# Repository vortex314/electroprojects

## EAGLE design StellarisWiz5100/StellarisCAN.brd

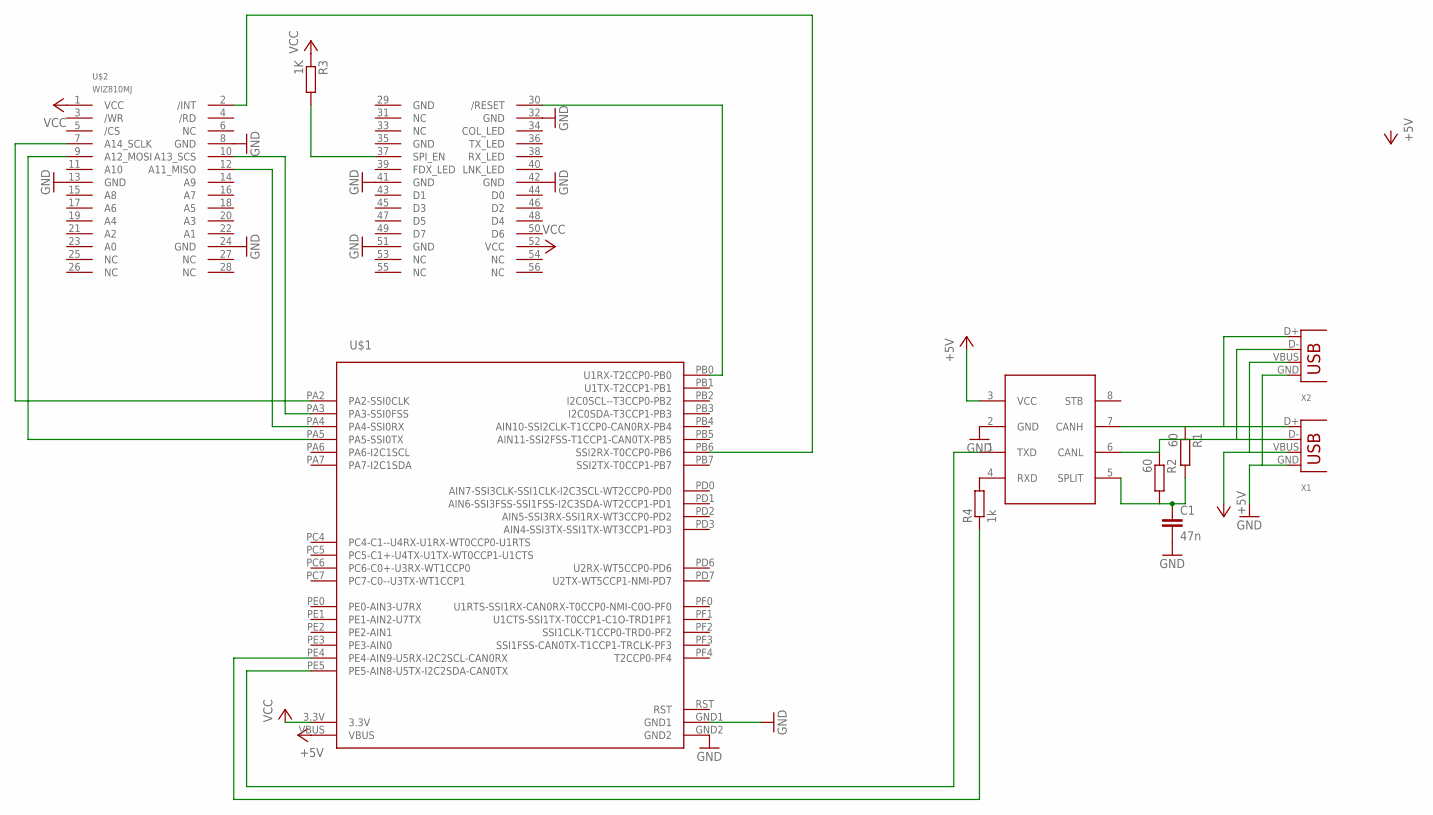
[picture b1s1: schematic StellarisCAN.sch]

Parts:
C1: 47n; C025-040X050
R1, R2: 60; 0207/7
R3: 1K; 0207/7
R4: 1k; 0207/7
U$1: STELLARIS-LAUNCHPADSTELLARIS-LAUNCHPAD-XL; LAUNCHPAD-XL
U$2: WIZ810MJ
U$3: TJA1040; SOIC8-N_MC
X1: USB-A-H
X2: USB-B-H

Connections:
3.3V: U$1.3.3V
+5V: U$1.VBUS, U$3.3 (VCC), X1.VBUS, X2.VBUS
GND: C1.2, U$1.GND1, U$1.GND2, U$2.8 (GND), U$2.13 (GND), U$2.24 (GND), U$2.32 (GND), U$2.41 (GND), U$2.42 (GND), U$2.51 (GND), U$3.2 (GND), X1.GND, X2.GND
unnamed: U$1.PB0 (U1RX-T2CCP0-PB0), U$2.30 (/RESET)
unnamed: R4.2, U$3.4 (RXD)
unnamed: U$1.PA2 (PA2-SSI0CLK), U$2.7 (A14_SCLK)
unnamed: R4.1, U$1.PE4 (PE4-AIN9-U5RX-I2C2SCL-CAN0RX)
unnamed: R1.1, U$3.7 (CANH), X1.D+, X2.D+
unnamed: U$1.PA5 (PA5-SSI0TX), U$2.9 (A12_MOSI)
unnamed: U$1.PE5 (PE5-AIN8-U5TX-I2C2SDA-CAN0TX), U$3.1 (TXD)
unnamed: U$1.PA4 (PA4-SSI0RX), U$2.12 (A11_MISO)
unnamed: U$1.PA3 (PA3-SSI0FSS), U$2.10 (A13_SCS)
unnamed: R3.2, U$2.37 (SPI_EN)
unnamed: C1.1, R1.2, R2.2, U$3.5 (SPLIT)
unnamed: R2.1, U$3.6 (CANL), X1.D-, X2.D-
unnamed: U$1.PB6 (SSI2RX-T0CCP0-PB6), U$2.2 (/INT)
RST: U$1.RST
VCC: R3.1, U$2.1 (VCC), U$2.52 (VCC)

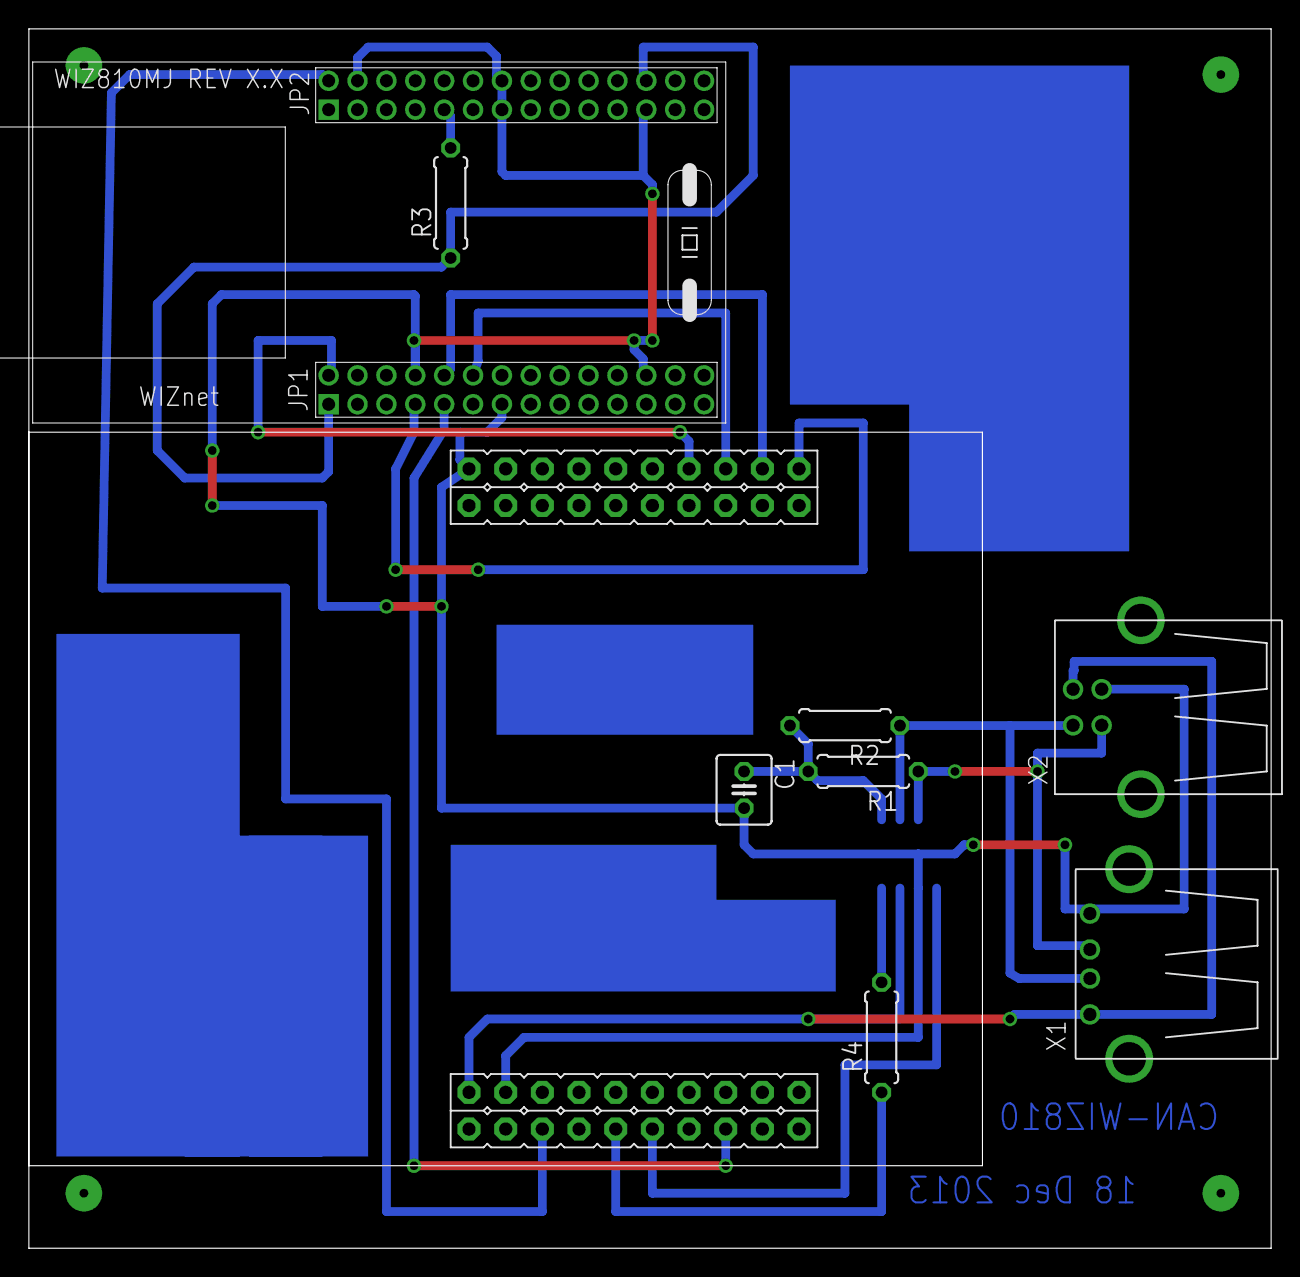
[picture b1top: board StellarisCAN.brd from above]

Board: 2 copper layers, 86.0 x 84.4 mm, 10 parts (1 on the bottom side), 16 nets.

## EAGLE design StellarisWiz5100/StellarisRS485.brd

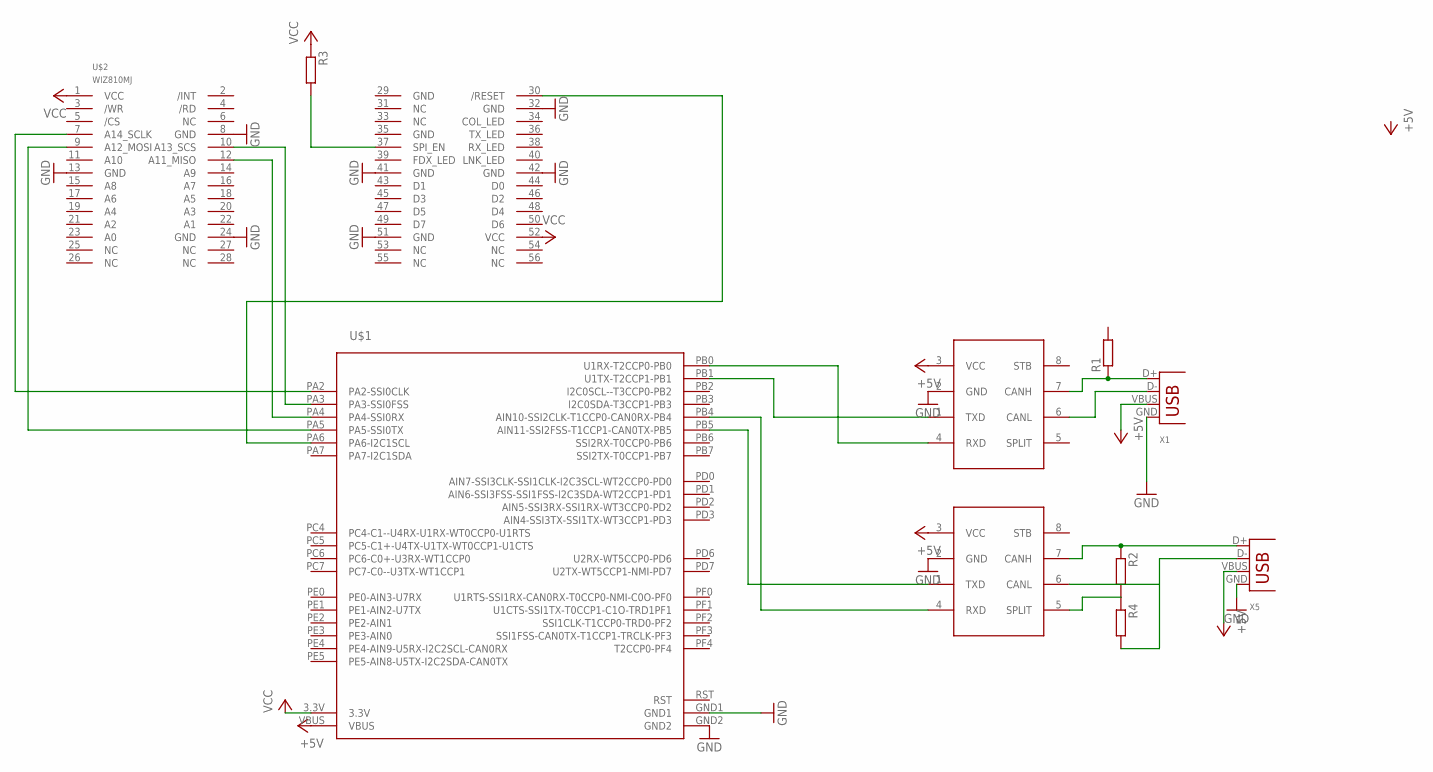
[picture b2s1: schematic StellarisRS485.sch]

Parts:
R1, R2, R3, R4: R-EU_0207/7; 0207/7
U$1: STELLARIS-LAUNCHPADSTELLARIS-LAUNCHPAD-XL; LAUNCHPAD-XL
U$2: WIZ810MJ
U$3, U$4: TJA1040; SOIC8-N_MC
X1, X5: USB-A-H

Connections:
3.3V: U$1.3.3V
+5V: U$1.VBUS, U$3.3 (VCC), U$4.3 (VCC), X1.VBUS, X5.VBUS
GND: U$1.GND1, U$1.GND2, U$2.8 (GND), U$2.13 (GND), U$2.24 (GND), U$2.32 (GND), U$2.41 (GND), U$2.42 (GND), U$2.51 (GND), U$3.2 (GND), U$4.2 (GND), X1.GND, X5.GND
unnamed: U$1.PA6 (PA6-I2C1SCL), U$2.30 (/RESET)
unnamed: R1.1, U$3.7 (CANH), X1.D+
unnamed: U$1.PA2 (PA2-SSI0CLK), U$2.7 (A14_SCLK)
unnamed: U$3.6 (CANL), X1.D-
unnamed: R2.1, U$4.7 (CANH), X5.D+
unnamed: U$1.PA5 (PA5-SSI0TX), U$2.9 (A12_MOSI)
unnamed: U$1.PB1 (U1TX-T2CCP1-PB1), U$3.1 (TXD)
unnamed: U$1.PA4 (PA4-SSI0RX), U$2.12 (A11_MISO)
unnamed: U$1.PA3 (PA3-SSI0FSS), U$2.10 (A13_SCS)
unnamed: R3.2, U$2.37 (SPI_EN)
unnamed: R2.2, R4.1, U$4.5 (SPLIT)
unnamed: U$1.PB0 (U1RX-T2CCP0-PB0), U$3.4 (RXD)
unnamed: R4.2, U$4.6 (CANL), X5.D-
unnamed: U$1.PB5 (AIN11-SSI2FSS-T1CCP1-CAN0TX-PB5), U$4.1 (TXD)
unnamed: U$1.PB4 (AIN10-SSI2CLK-T1CCP0-CAN0RX-PB4), U$4.4 (RXD)
RST: U$1.RST
VCC: R3.1, U$2.1 (VCC), U$2.52 (VCC)

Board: 2 copper layers, 10 parts (2 on the bottom side), 18 nets, no tracks yet.

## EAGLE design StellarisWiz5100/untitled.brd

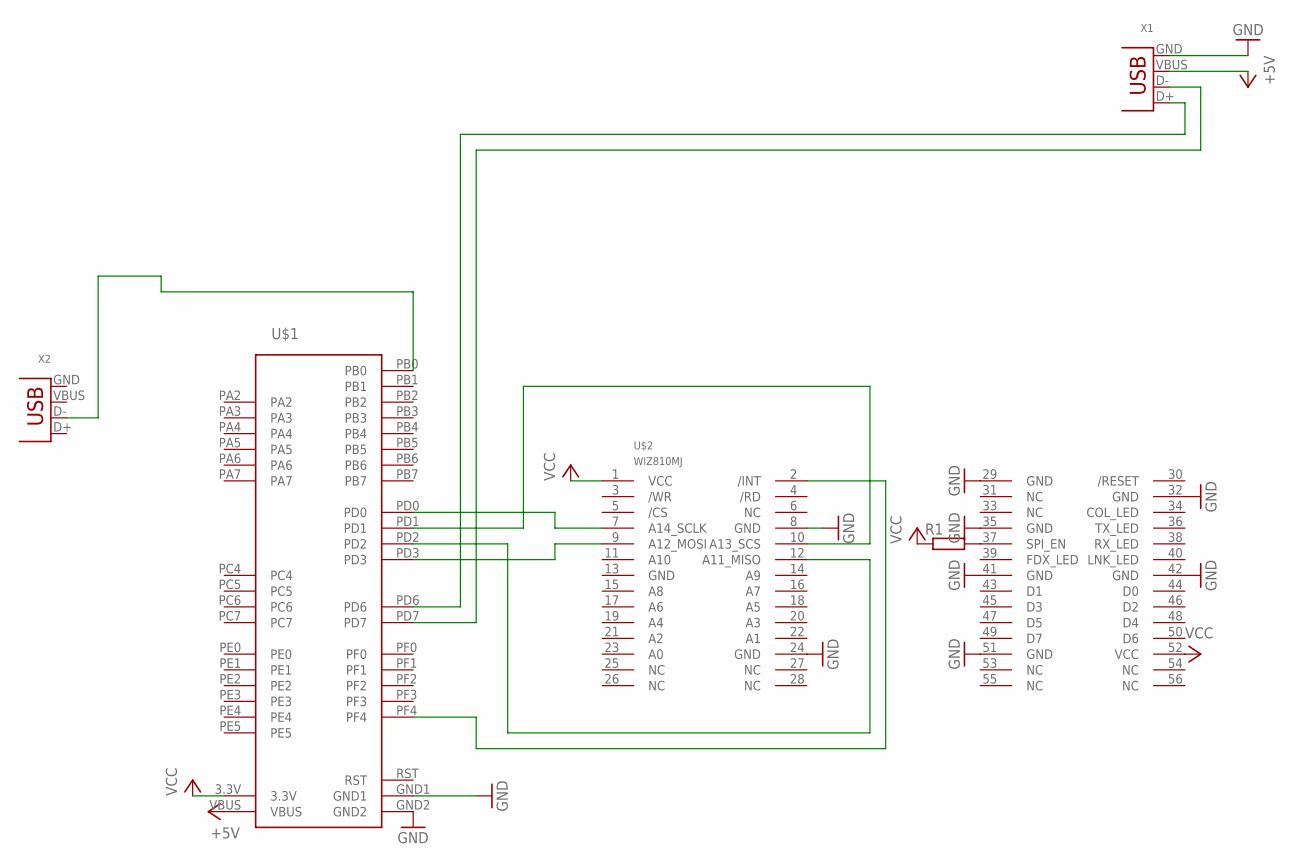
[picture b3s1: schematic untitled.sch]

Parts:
R1: R-EU_0204/5; 0204/5
U$1: STELLARIS-LAUNCHPADSTELLARIS-LAUNCHPAD-XL; LAUNCHPAD-XL
U$2: WIZ810MJ
X1, X2: USB-A-H

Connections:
+5V: U$1.VBUS, X1.VBUS
GND: U$1.GND1, U$1.GND2, U$2.8 (GND), U$2.24 (GND), U$2.29 (GND), U$2.32 (GND), U$2.35 (GND), U$2.41 (GND), U$2.42 (GND), U$2.51 (GND), X1.GND
unnamed: U$1.PD0, U$2.7 (A14_SCLK)
unnamed: R1.2, U$2.37 (SPI_EN)
unnamed: U$1.PD3, U$2.9 (A12_MOSI)
unnamed: U$1.PD2, U$2.12 (A11_MISO)
unnamed: U$1.PD1, U$2.10 (A13_SCS)
unnamed: U$1.PF4, U$2.2 (/INT)
unnamed: U$1.PD6, X1.D+
unnamed: U$1.PD7, X1.D-
unnamed: U$1.PB0, X2.D-
RST: U$1.RST
VCC: R1.1, U$1.3.3V, U$2.1 (VCC), U$2.52 (VCC)

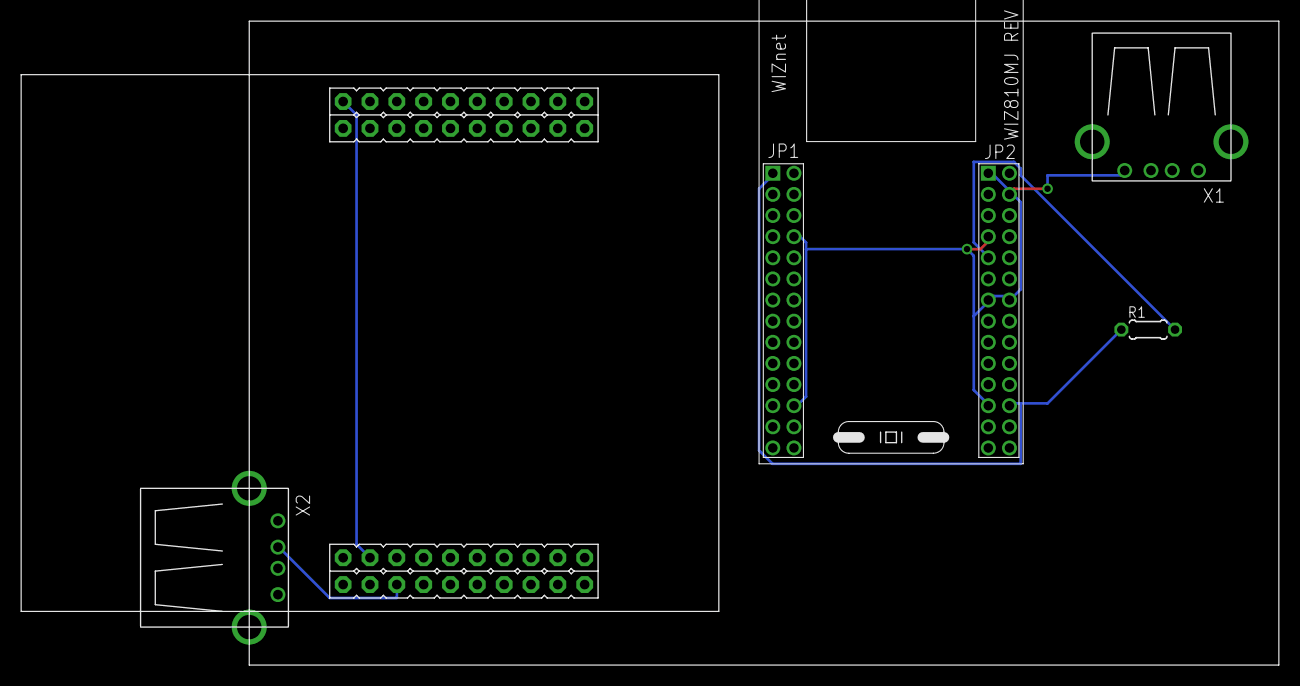
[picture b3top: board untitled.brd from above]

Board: 2 copper layers, 119.0 x 61.0 mm, 5 parts (0 on the bottom side), 12 nets.

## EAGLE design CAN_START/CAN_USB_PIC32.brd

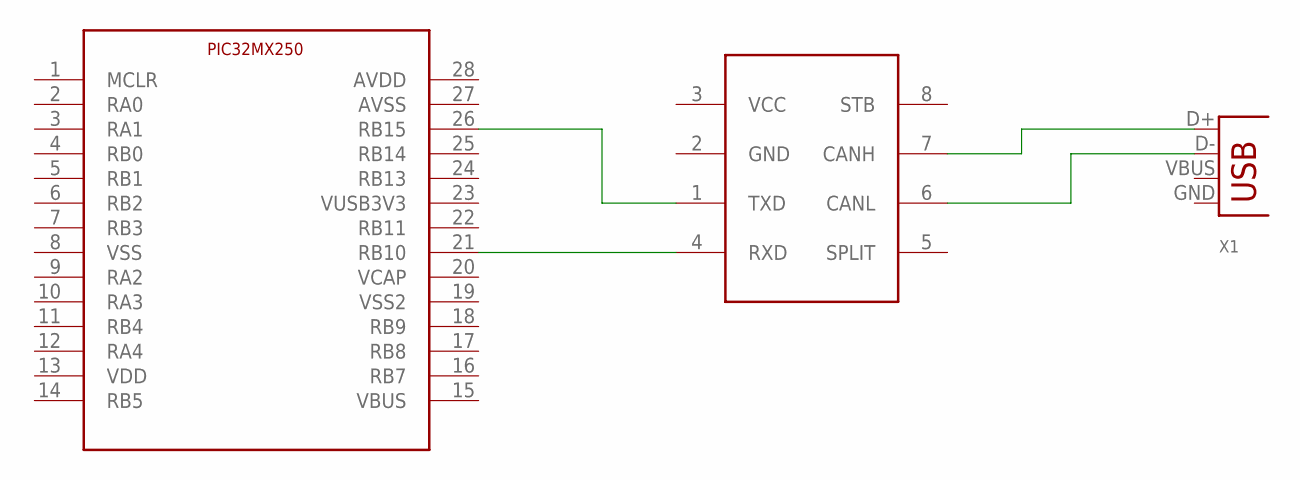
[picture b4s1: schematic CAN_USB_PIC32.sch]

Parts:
U$1: TJA1040; SOIC8-N_MC
U$2: PIC32MX250SOIC; SOIC28
X1: USB-B-H

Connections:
GND: U$1.2 (GND)
unnamed: U$1.7 (CANH), X1.D+
unnamed: U$1.6 (CANL), X1.D-
unnamed: U$1.1 (TXD), U$2.26 (RB15)
unnamed: U$1.4 (RXD), U$2.21 (RB10)
VCC: U$1.3 (VCC)
VDD: U$2.13 (VDD)
VSS: U$2.8 (VSS)

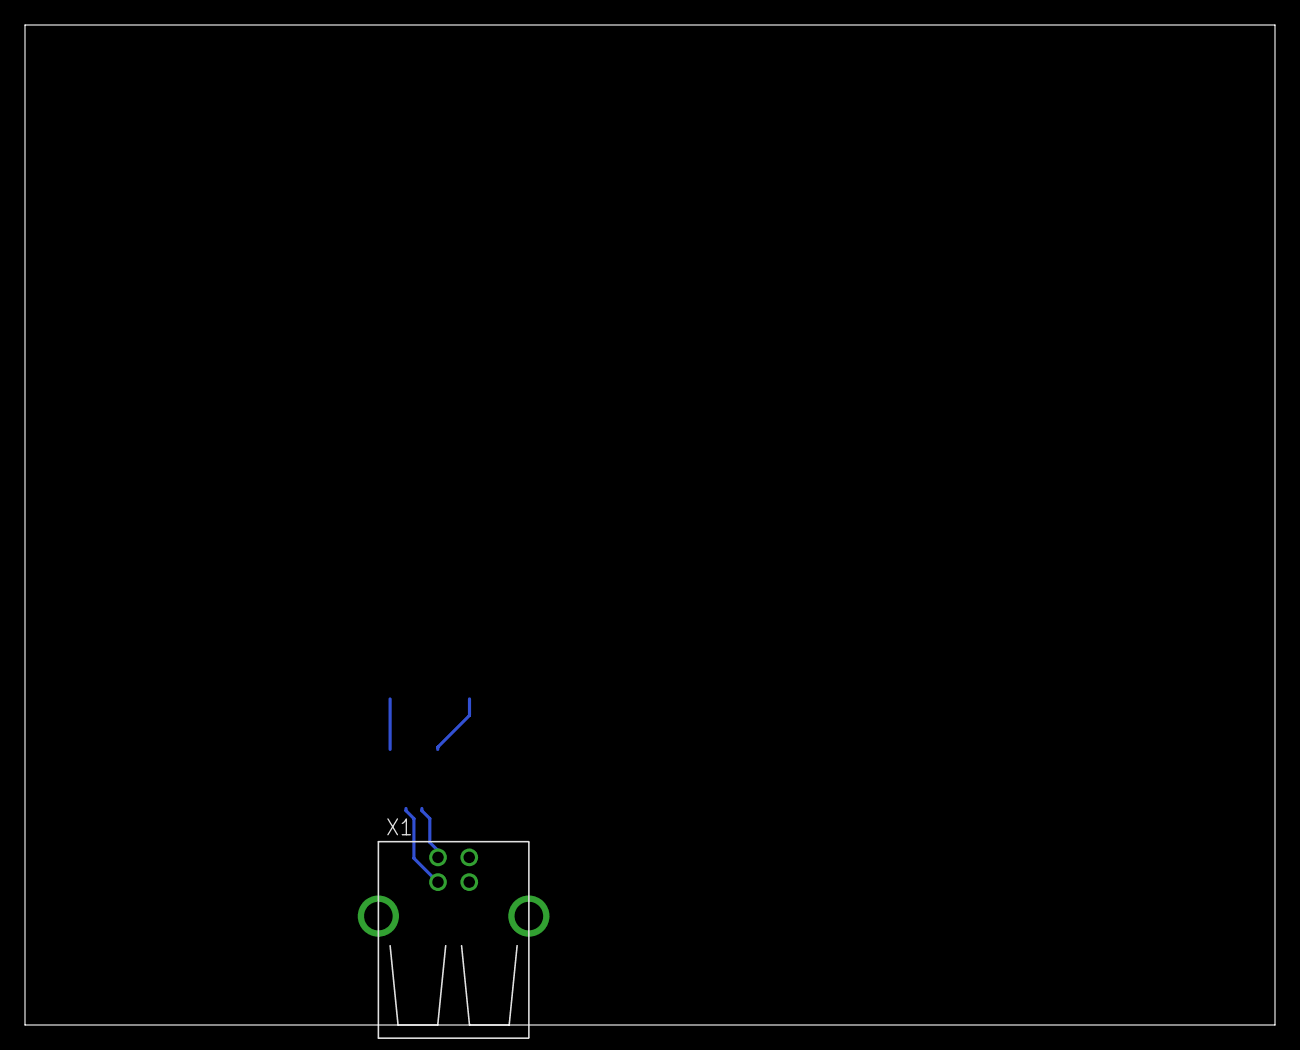
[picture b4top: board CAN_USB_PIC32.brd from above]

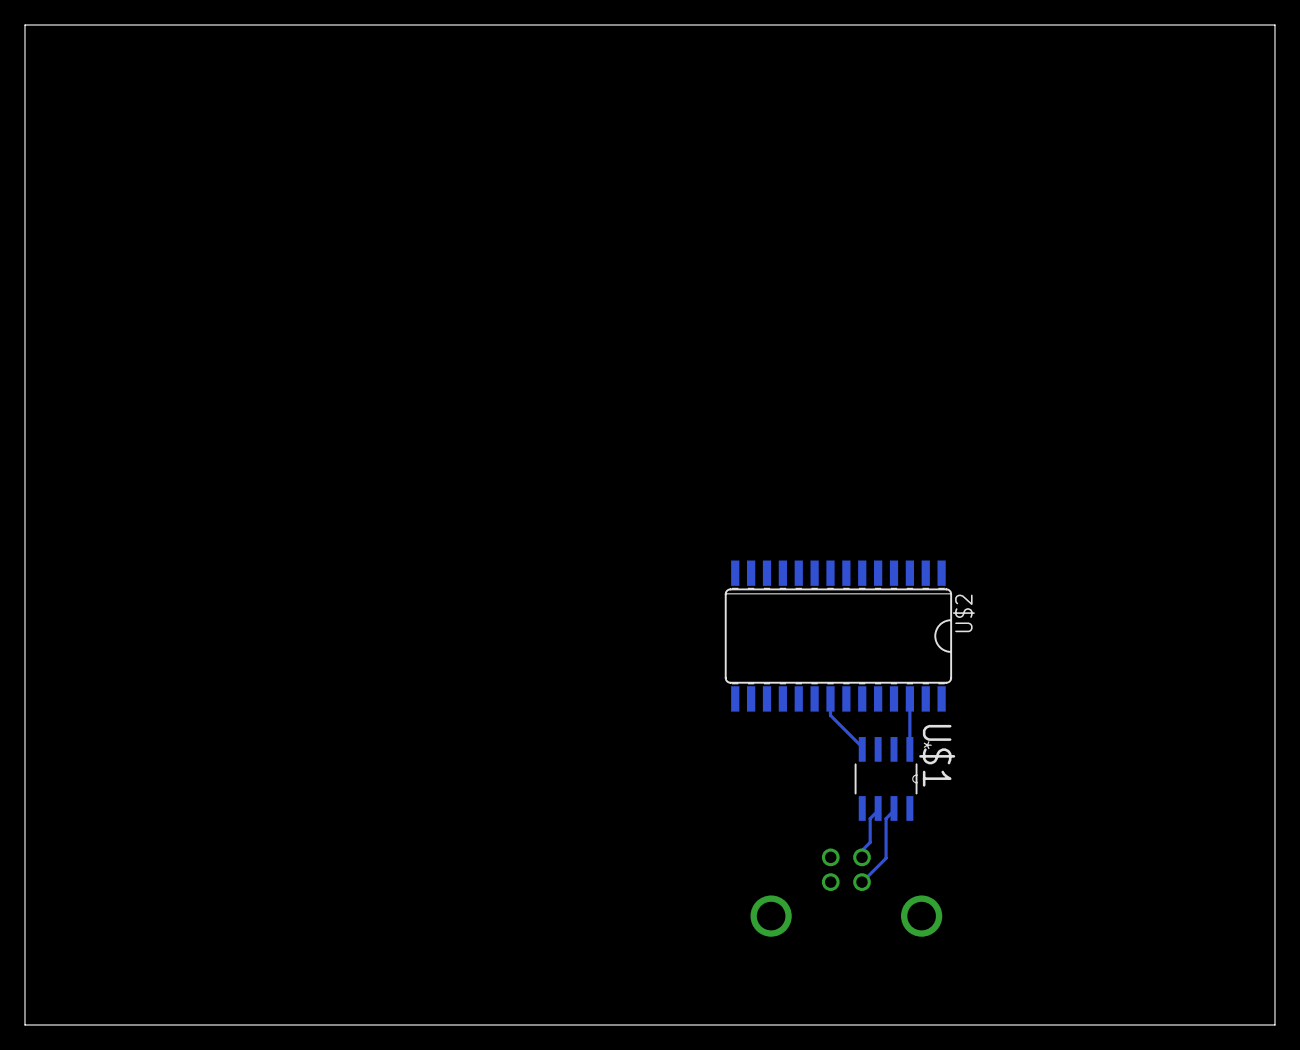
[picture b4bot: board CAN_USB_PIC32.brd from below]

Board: 2 copper layers, 100.0 x 80.0 mm, 3 parts (2 on the bottom side), 4 nets.

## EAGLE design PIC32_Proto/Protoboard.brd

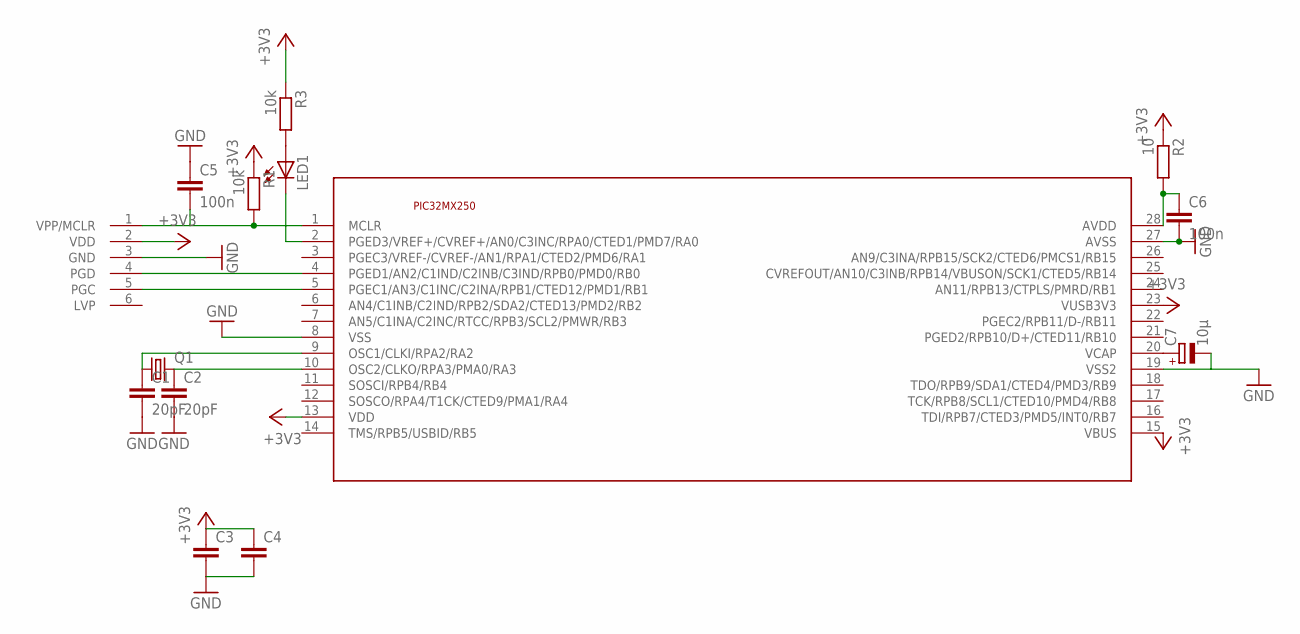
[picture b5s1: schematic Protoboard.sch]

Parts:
C1, C2: 20pF; C050-024X044
C3, C4: C-EU050-024X044; C050-024X044
C5, C6: 100n; C050-024X044
C7: 10µ; B45181B
LED1: LED5MM
Q1: CRYSTALTC26V; TC26V
R1, R3: 10k; 0207/10
R2: 10; 0207/10
U$2: ICSP-6_6P; 1X06-CLEANBIG
U$3: PIC32MX2XXSOIC; SOIC28

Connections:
+3V3: C3.1, C4.1, R1.1, R2.1, R3.1, U$2.2 (VDD), U$3.13 (VDD), U$3.15 (VBUS), U$3.23 (VUSB3V3)
GND: C1.2, C2.2, C3.2, C4.2, C5.1, C6.2, C7.-, U$2.3 (GND), U$3.8 (VSS), U$3.19 (VSS2), U$3.27 (AVSS)
unnamed: C2.1, Q1.2, U$3.10 (OSC2/CLKO/RPA3/PMA0/RA3)
unnamed: C5.2, R1.2, U$2.1 (VPP/MCLR), U$3.1 (MCLR)
unnamed: U$2.5 (PGC), U$3.5 (PGEC1/AN3/C1INC/C2INA/RPB1/CTED12/PMD1/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)
unnamed: C1.1, Q1.1, U$3.9 (OSC1/CLKI/RPA2/RA2)
unnamed: U$2.4 (PGD), U$3.4 (PGED1/AN2/C1IND/C2INB/C3IND/RPB0/PMD0/R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)
unnamed: LED1.K (C), U$3.2 (PGED3/VREF+/CVREF+/AN0/C3INC/RPA0/CTED1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)
unnamed: C7.+, U$3.20 (VCAP)
unnamed: C6.1, R2.2, U$3.28 (AVDD)
unnamed: LED1.A, R3.2

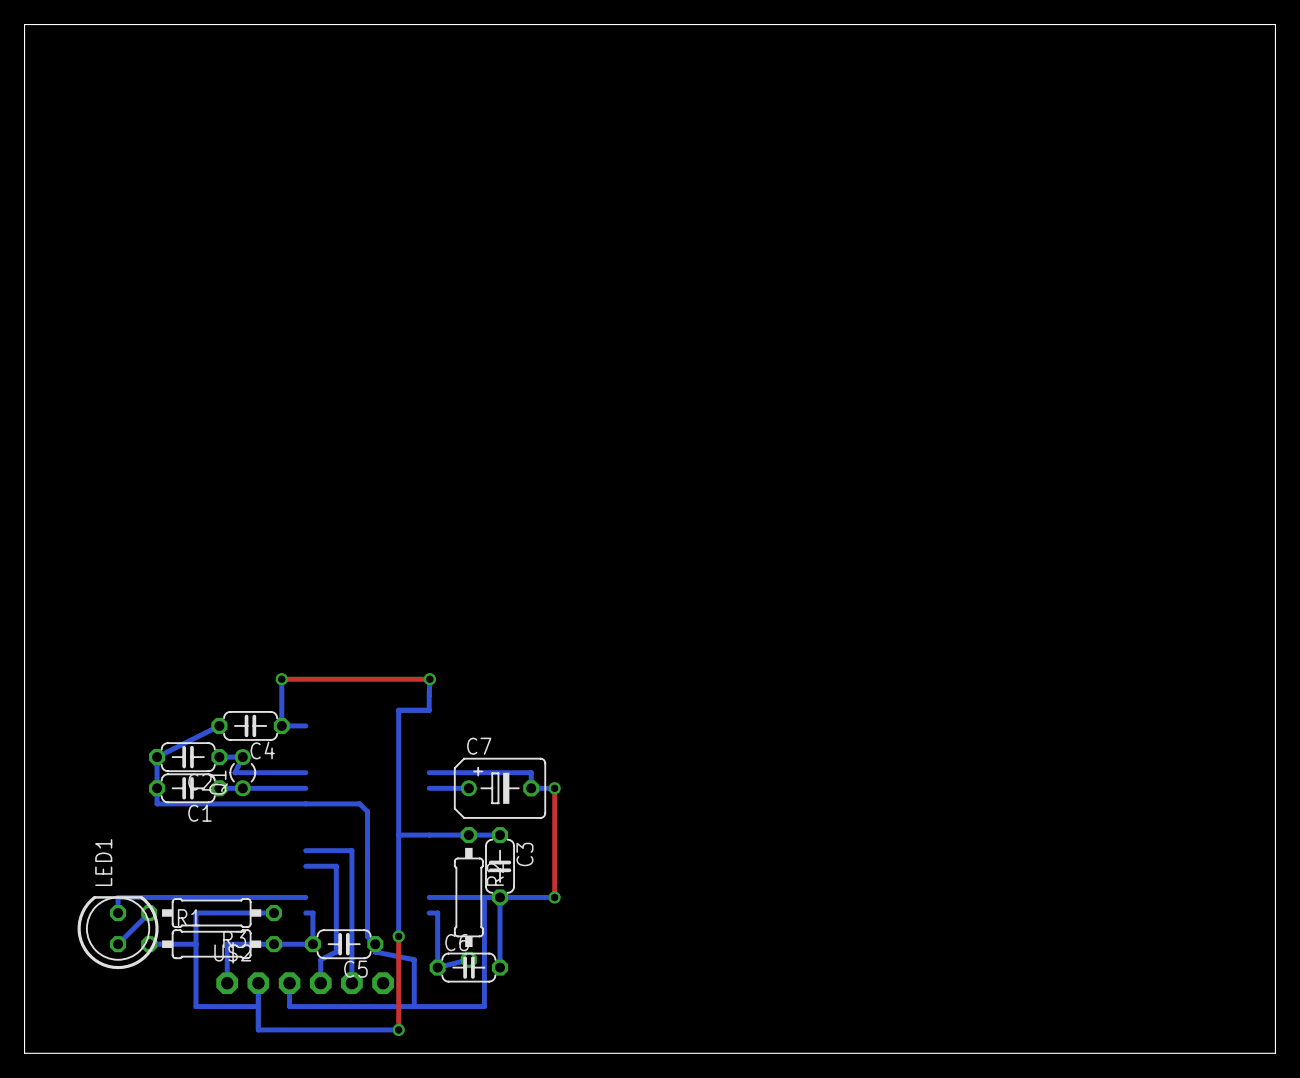
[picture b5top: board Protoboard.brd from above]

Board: 2 copper layers, 101.9 x 83.8 mm, 14 parts (1 on the bottom side), 11 nets.

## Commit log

2015-03-18 Migrating wiki contents from Google Code
2017-12-07 Added Untitled Library.xml
